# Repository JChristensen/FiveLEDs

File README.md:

# Five LEDs Puzzle
https://github.com/JChristensen/FiveLEDs  
README file  
Jack Christensen  
Jan-2021

## License
  
Five LEDs Puzzle by Jack Christensen and the original project by David Johnson-Davies are both licensed under under a [Creative Commons Attribution 4.0 International License](http://creativecommons.org/licenses/by/4.0/).

See the original project at:  
https://github.com/technoblogy/five-leds-puzzle  
http://www.technoblogy.com/show?3EL5

## Introduction
This is just my spin on David Johnson-Davies' Five LEDs Puzzle. The [circuit](https://raw.githubusercontent.com/JChristensen/FiveLEDs/master/extras/schematic.png) is modified slightly, to use an ATtiny84A microcontroller, and the [PC board design](https://raw.githubusercontent.com/JChristensen/FiveLEDs/master/extras/board.png) is new, to accommodate SMT components and an AA battery holder.

## Instructions
The object of the puzzle is to get all the LEDs to remain lit. Each LED lights up briefly when the corresponding button below it is pressed, but an LED only stays lit under certain conditions; to solve the puzzle you need to work out what the rule is.

The puzzle can be solved by pressing one button at a time; there is no benefit in pressing combinations. To return the puzzle to the start, with all LEDs off, press the RESET button.

If no button is pressed for 30 seconds, the puzzle will automatically turn itself off. Press any button to turn it back on. The LEDs will then be in the same state as when it turned off.

## Circuit design
A bill of materials is available at [Mouser Electronics](https://www.mouser.com/ProjectManager/ProjectDetail.aspx?AccessID=cfd9324946) and also in [this repo](https://github.com/JChristensen/FiveLEDs/blob/master/extras/bom.csv).

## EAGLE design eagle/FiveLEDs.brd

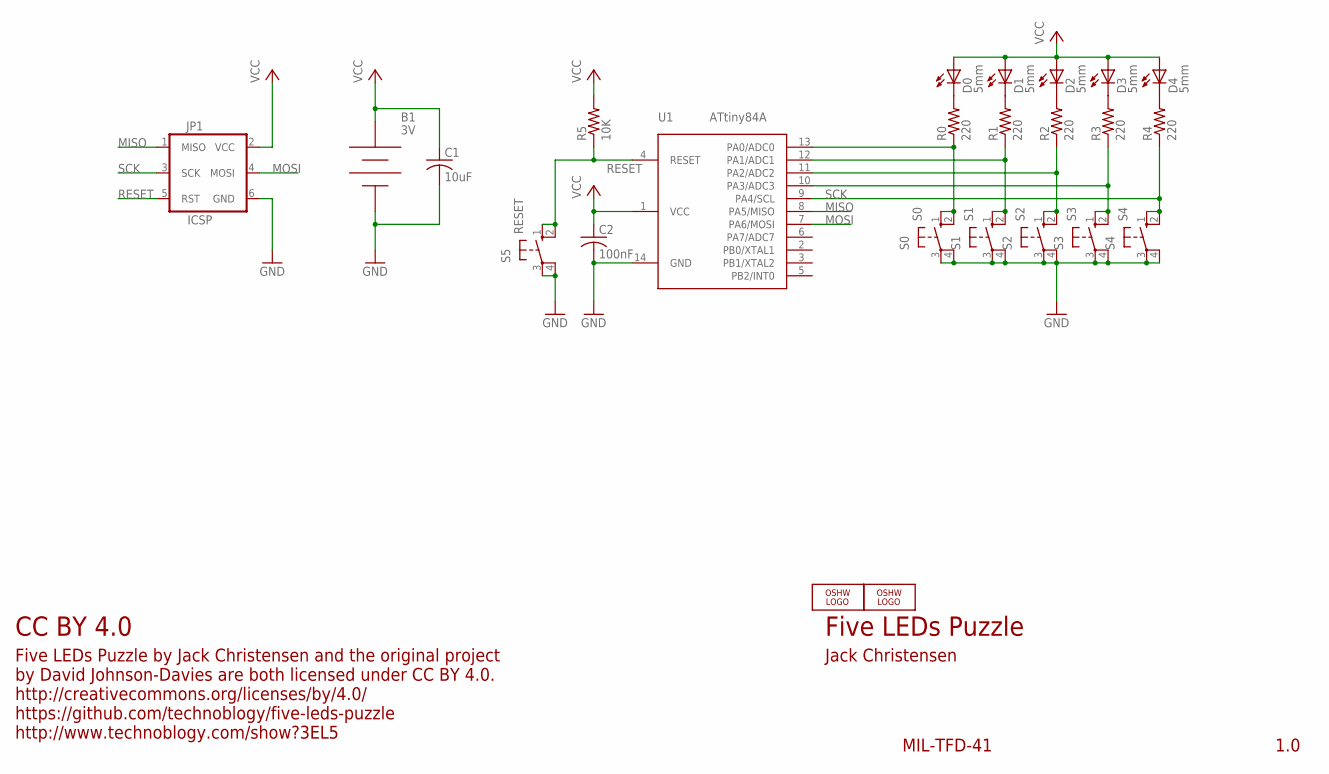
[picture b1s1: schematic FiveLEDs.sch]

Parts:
B1: 3V; KEYSTONE-2462-NO-HOLES
C1: 10uF; M0805
C2: 100nF; M0805
D0, D1, D2, D3, D4: 5mm; LED5MM
JP1: ICSP; 2X3_LOCK
LOGO1: OSHW_LOGO_8MILX0150-NT; OSHW_8X150_NOTEXT
LOGO3: OSHW_LOGO_8MILX0100-NT; OSHW_8X100_NOTEXT
R0, R1, R2, R3, R4: 220; M0805
R5: 10K; M0805
S0: S0; B3F-10XXOCT
S1: S1; B3F-10XXOCT
S2: S2; B3F-10XXOCT
S3: S3; B3F-10XXOCT
S4: S4; B3F-10XXOCT
S5: RESET; B3F-10XXOCT
U1: ATtiny84A; SO14

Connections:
GND: B1.NEG, C1.2, C2.2, JP1.6 (GND), S0.3, S0.4 (P1), S1.3, S1.4 (P1), S2.3, S2.4 (P1), S3.3, S3.4 (P1), S4.3, S4.4 (P1), S5.3, S5.4 (P1), U1.14 (GND)
MISO: JP1.1 (MISO), U1.8 (PA5/MISO)
MOSI: JP1.4 (MOSI), U1.7 (PA6/MOSI)
unnamed: D0.K (C), R0.2
unnamed: R0.1, S0.1 (S), S0.2 (S1), U1.13 (PA0/ADC0)
unnamed: D1.K (C), R1.2
unnamed: R1.1, S1.1 (S), S1.2 (S1), U1.12 (PA1/ADC1)
unnamed: D2.K (C), R2.2
unnamed: R2.1, S2.1 (S), S2.2 (S1), U1.11 (PA2/ADC2)
unnamed: D3.K (C), R3.2
unnamed: R3.1, S3.1 (S), S3.2 (S1), U1.10 (PA3/ADC3)
unnamed: D4.K (C), R4.2
RESET: JP1.5 (RST), R5.1, S5.1 (S), S5.2 (S1), U1.4 (RESET)
SCK: JP1.3 (SCK), R4.1, S4.1 (S), S4.2 (S1), U1.9 (PA4/SCL)
VCC: B1.POS, C1.1, C2.1, D0.A, D1.A, D2.A, D3.A, D4.A, JP1.2 (VCC), R5.2, U1.1 (VCC)

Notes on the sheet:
Five LEDs Puzzle
Jack Christensen
MIL-TFD-41
1.0
CC BY 4.0
Five LEDs Puzzle by Jack Christensen and the original project by David Johnson-Davies are both licensed under CC BY 4.0. http://creativecommons.org/licenses/by/4.0/ https://github.com/technoblogy/five-leds-puzzle http://www.technoblogy.com/show?3EL5

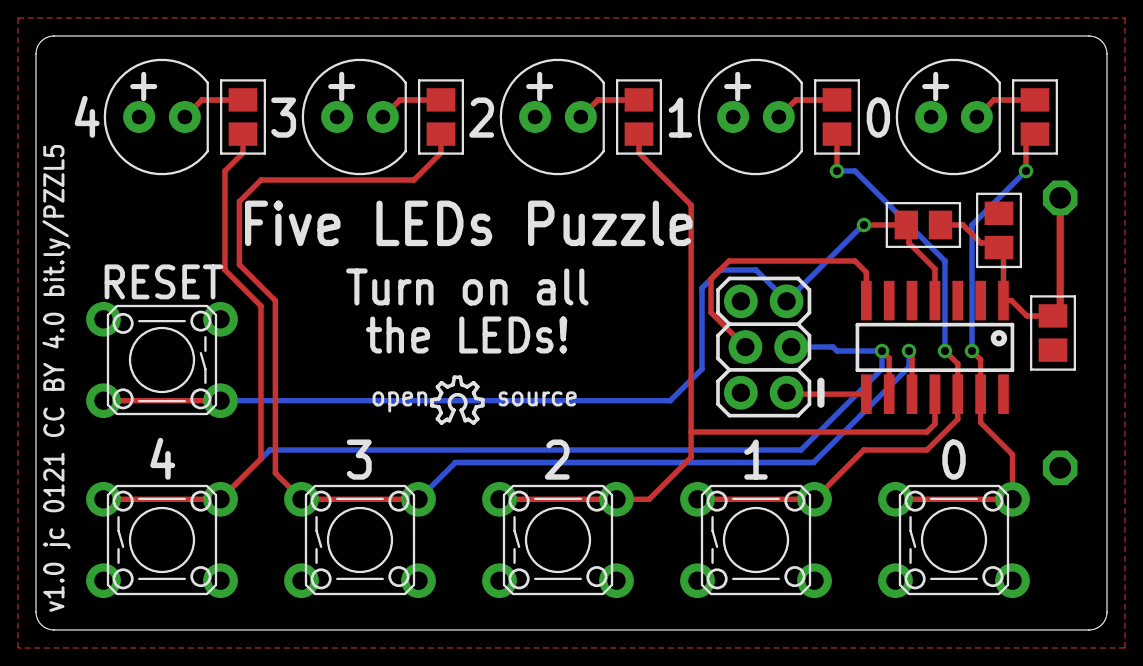
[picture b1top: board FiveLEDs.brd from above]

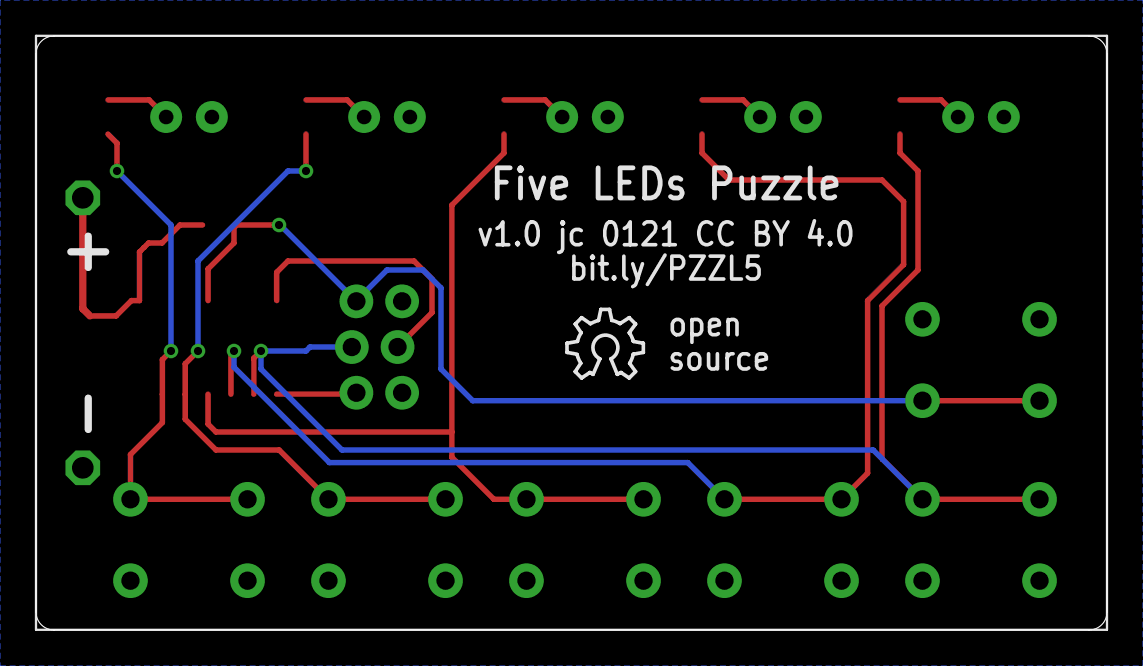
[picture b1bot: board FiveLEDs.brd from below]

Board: 2 copper layers, 59.5 x 33.0 mm, 24 parts (2 on the bottom side), 15 nets.

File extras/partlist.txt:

Partlist

Exported from FiveLEDs.sch at 1/6/21 11:22 PM

EAGLE Version 9.6.2 Copyright (c) 1988-2020 Autodesk, Inc.

Assembly variant: 

Part     Value          Device                Package                Library  Sheet

B1       3V             BATTERY-2AANOHOLES    KEYSTONE-2462-NO-HOLES _jc      1
C1       10uF           C-USM0805             M0805                  _jc      1
C2       100nF          C-USM0805             M0805                  _jc      1
D0       5mm            LED5MM                LED5MM                 _jc      1
D1       5mm            LED5MM                LED5MM                 _jc      1
D2       5mm            LED5MM                LED5MM                 _jc      1
D3       5mm            LED5MM                LED5MM                 _jc      1
D4       5mm            LED5MM                LED5MM                 _jc      1
JP1      ICSP           AVR_SPI_PRG_62X3_LOCK 2X3_LOCK               _jc      1
R0       220            R-US_M0805            M0805                  _jc      1
R1       220            R-US_M0805            M0805                  _jc      1
R2       220            R-US_M0805            M0805                  _jc      1
R3       220            R-US_M0805            M0805                  _jc      1
R4       220            R-US_M0805            M0805                  _jc      1
R5       10K            R-US_M0805            M0805                  _jc      1
S0       S0             10-XXOCT              B3F-10XXOCT            _jc      1
S1       S1             10-XXOCT              B3F-10XXOCT            _jc      1
S2       S2             10-XXOCT              B3F-10XXOCT            _jc      1
S3       S3             10-XXOCT              B3F-10XXOCT            _jc      1
S4       S4             10-XXOCT              B3F-10XXOCT            _jc      1
S5       RESET          10-XXOCT              B3F-10XXOCT            _jc      1
U1       ATtiny84A      ATTINYX4SO14          SO14                   _jc      1

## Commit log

2021-01-06 Initial commit.
2021-01-07 Update README file.
2021-01-16 Add sketch, Eagle files, images, BOM.
2021-01-16 Update README.

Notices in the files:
eagle/FiveLEDs.brd:
v1.0 jc 0121 CC BY 4.0 bit.ly/PZZL5
